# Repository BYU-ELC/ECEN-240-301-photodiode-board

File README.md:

# ECEN-240-301-photodiode-board

Welcome! This repository holds the files for the ECEN 240/301 photodiode board

## Purpose

This repository is meant primarily for internal communication. Under normal circumstances, students of ECEN 240/301 shouldn't need to download and manipulate these files. Although, they are welcome to do so if the need arises.

## Associated Software

This board was designed on Autodesk Eagle

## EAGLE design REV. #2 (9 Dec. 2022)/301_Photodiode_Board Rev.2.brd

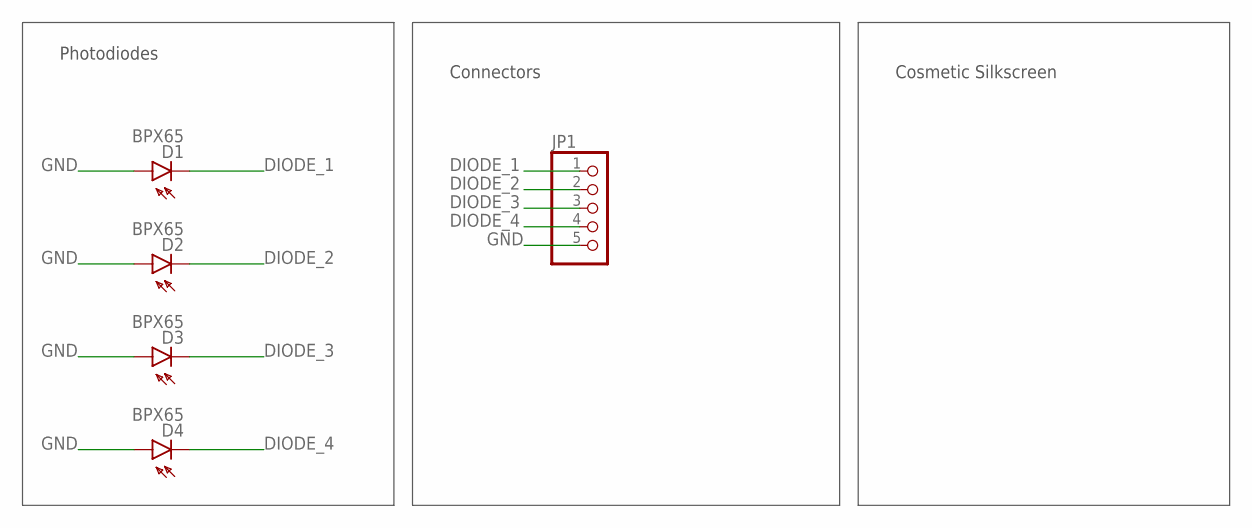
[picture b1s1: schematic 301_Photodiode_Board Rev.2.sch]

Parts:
D1, D2, D3, D4: BPX65
JP1: PINHD-1X5; 1X05

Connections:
DIODE_1: D1.K (C), JP1.1
DIODE_2: D2.K (C), JP1.2
DIODE_3: D3.K (C), JP1.3
DIODE_4: D4.K (C), JP1.4
GND: D1.A, D2.A, D3.A, D4.A, JP1.5

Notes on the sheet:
Photodiodes
Connectors
Cosmetic Silkscreen

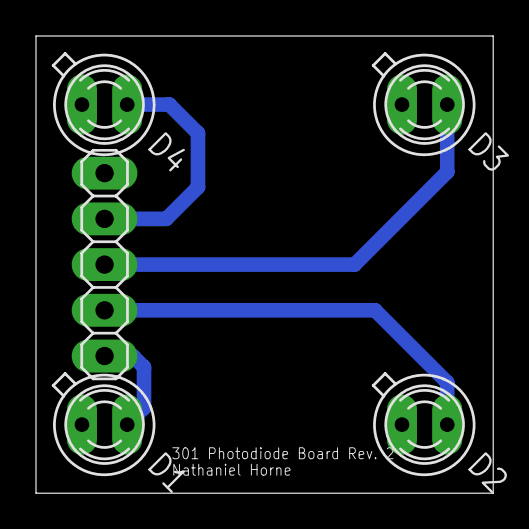
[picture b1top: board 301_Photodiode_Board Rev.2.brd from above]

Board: 2 copper layers, 25.4 x 25.4 mm, 5 parts (0 on the bottom side), 5 nets.

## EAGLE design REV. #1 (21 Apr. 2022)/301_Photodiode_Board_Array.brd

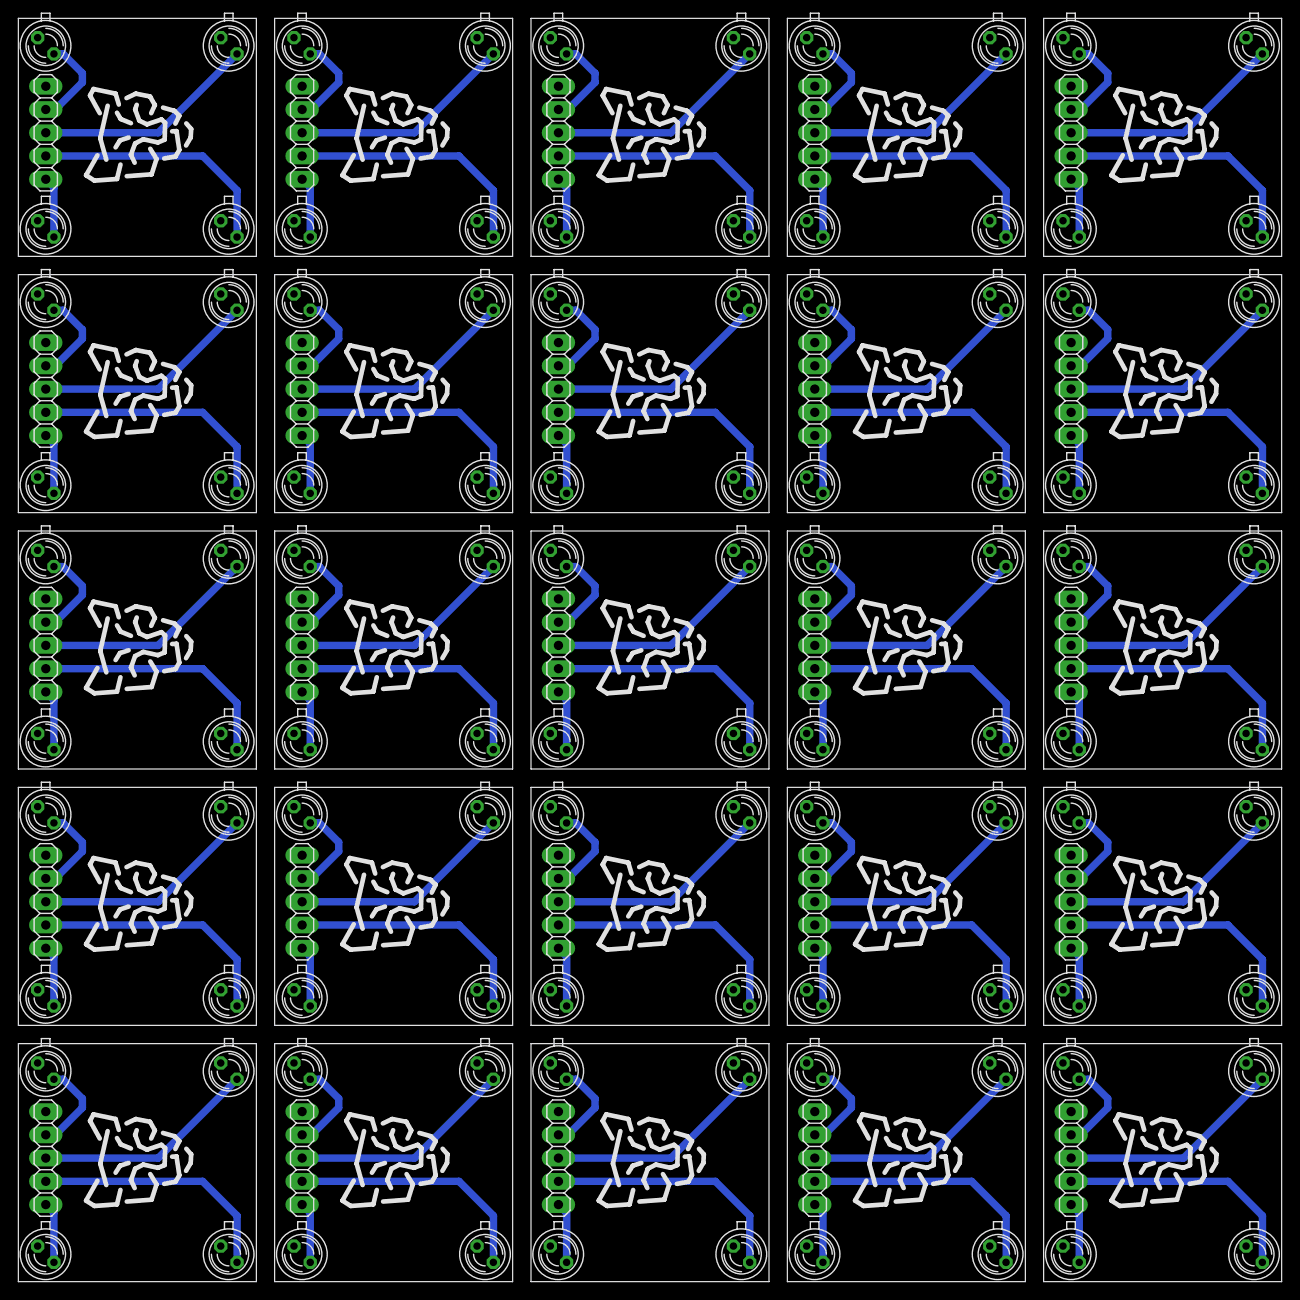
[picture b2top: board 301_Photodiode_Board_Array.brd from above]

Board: 2 copper layers, 138.0 x 138.0 mm, 150 parts (0 on the bottom side), 125 nets.

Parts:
D1, D2, D3, D4, D5, D6, D7, D8, D9, D10, D11, D12, D13, D14, D15, D16, D17, D18, D19, D20, D21, D22, D23, D24, D25, D26, D27, D28, D29, D30, D31, D32, D33, D34, D35, D36, D37, D38, D39, D40, D41, D42, D43, D44, D45, D46, D47, D48, D49, D50, D51, D52, D53, D54, D55, D56, D57, D58, D59, D60, D61, D62, D63, D64, D65, D66, D67, D68, D69, D70, D71, D72, D73, D74, D75, D76, D77, D78, D79, D80, D81, D82, D83, D84, D85, D86, D87, D88, D89, D90, D91, D92, D93, D94, D95, D96, D97, D98, D99, D100: BPX65
JP1, JP2, JP3, JP4, JP5, JP6, JP7, JP8, JP9, JP10, JP11, JP12, JP13, JP14, JP15, JP16, JP17, JP18, JP19, JP20, JP21, JP22, JP23, JP24, JP25: 1X05
U$1, U$2, U$3, U$4, U$5, U$6, U$7, U$8, U$9, U$10, U$11, U$12, U$13, U$14, U$15, U$16, U$17, U$18, U$19, U$20, U$21, U$22, U$23, U$24, U$25: COUGAR_LOGO_LARGE; LRG_COUGAR

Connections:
DIODE_1: D1.K, JP1.1
DIODE_2: D2.K, JP1.2
DIODE_3: D3.K, JP1.3
DIODE_4: D4.K, JP1.4
DIODE_5: D5.K, JP2.1
DIODE_6: D6.K, JP2.2
DIODE_7: D7.K, JP2.3
DIODE_8: D8.K, JP2.4
DIODE_9: D9.K, JP3.1
DIODE_10: D10.K, JP3.2
DIODE_11: D11.K, JP3.3
DIODE_12: D12.K, JP3.4
DIODE_13: D13.K, JP4.1
DIODE_14: D14.K, JP4.2
DIODE_15: D15.K, JP4.3
DIODE_16: D16.K, JP4.4
DIODE_17: D17.K, JP5.1
DIODE_18: D18.K, JP5.2
DIODE_19: D19.K, JP5.3
DIODE_20: D20.K, JP5.4
DIODE_21: D21.K, JP6.1
DIODE_22: D22.K, JP6.2
DIODE_23: D23.K, JP6.3
DIODE_24: D24.K, JP6.4
DIODE_25: D25.K, JP7.1
DIODE_26: D26.K, JP7.2
DIODE_27: D27.K, JP7.3
DIODE_28: D28.K, JP7.4
DIODE_29: D29.K, JP8.1
DIODE_30: D30.K, JP8.2
DIODE_31: D31.K, JP8.3
DIODE_32: D32.K, JP8.4
DIODE_33: D33.K, JP9.1
DIODE_34: D34.K, JP9.2
DIODE_35: D35.K, JP9.3
DIODE_36: D36.K, JP9.4
DIODE_37: D37.K, JP10.1
DIODE_38: D38.K, JP10.2
DIODE_39: D39.K, JP10.3
DIODE_40: D40.K, JP10.4
DIODE_41: D41.K, JP11.1
DIODE_42: D42.K, JP11.2
DIODE_43: D43.K, JP11.3
DIODE_44: D44.K, JP11.4
DIODE_45: D45.K, JP12.1
DIODE_46: D46.K, JP12.2
DIODE_47: D47.K, JP12.3
DIODE_48: D48.K, JP12.4
DIODE_49: D49.K, JP13.1
DIODE_50: D50.K, JP13.2
DIODE_51: D51.K, JP13.3
DIODE_52: D52.K, JP13.4
DIODE_53: D53.K, JP14.1
DIODE_54: D54.K, JP14.2
DIODE_55: D55.K, JP14.3
DIODE_56: D56.K, JP14.4
DIODE_57: D57.K, JP15.1
DIODE_58: D58.K, JP15.2
DIODE_59: D59.K, JP15.3
DIODE_60: D60.K, JP15.4
DIODE_61: D61.K, JP16.1
DIODE_62: D62.K, JP16.2
DIODE_63: D63.K, JP16.3
DIODE_64: D64.K, JP16.4
DIODE_65: D65.K, JP17.1
DIODE_66: D66.K, JP17.2
DIODE_67: D67.K, JP17.3
DIODE_68: D68.K, JP17.4
DIODE_69: D69.K, JP18.1
DIODE_70: D70.K, JP18.2
DIODE_71: D71.K, JP18.3
DIODE_72: D72.K, JP18.4
DIODE_73: D73.K, JP19.1
DIODE_74: D74.K, JP19.2
DIODE_75: D75.K, JP19.3
DIODE_76: D76.K, JP19.4
DIODE_77: D77.K, JP20.1
DIODE_78: D78.K, JP20.2
DIODE_79: D79.K, JP20.3
DIODE_80: D80.K, JP20.4
DIODE_81: D81.K, JP21.1
DIODE_82: D82.K, JP21.2
DIODE_83: D83.K, JP21.3
DIODE_84: D84.K, JP21.4
DIODE_85: D85.K, JP22.1
DIODE_86: D86.K, JP22.2
DIODE_87: D87.K, JP22.3
DIODE_88: D88.K, JP22.4
DIODE_89: D89.K, JP23.1
DIODE_90: D90.K, JP23.2
DIODE_91: D91.K, JP23.3
DIODE_92: D92.K, JP23.4
DIODE_93: D93.K, JP24.1
DIODE_94: D94.K, JP24.2
DIODE_95: D95.K, JP24.3
DIODE_96: D96.K, JP24.4
DIODE_97: D97.K, JP25.1
DIODE_98: D98.K, JP25.2
DIODE_99: D99.K, JP25.3
DIODE_100: D100.K, JP25.4
GND: D1.A, D2.A, D3.A, D4.A, JP1.5
GND1: D5.A, D6.A, D7.A, D8.A, JP2.5
GND2: D9.A, D10.A, D11.A, D12.A, JP3.5
GND3: D13.A, D14.A, D15.A, D16.A, JP4.5
GND4: D17.A, D18.A, D19.A, D20.A, JP5.5
GND5: D21.A, D22.A, D23.A, D24.A, JP6.5
GND6: D25.A, D26.A, D27.A, D28.A, JP7.5
GND7: D29.A, D30.A, D31.A, D32.A, JP8.5
GND8: D33.A, D34.A, D35.A, D36.A, JP9.5
GND9: D37.A, D38.A, D39.A, D40.A, JP10.5
GND10: D41.A, D42.A, D43.A, D44.A, JP11.5
GND11: D45.A, D46.A, D47.A, D48.A, JP12.5
GND12: D49.A, D50.A, D51.A, D52.A, JP13.5
GND13: D53.A, D54.A, D55.A, D56.A, JP14.5
GND14: D57.A, D58.A, D59.A, D60.A, JP15.5
GND15: D61.A, D62.A, D63.A, D64.A, JP16.5
GND16: D65.A, D66.A, D67.A, D68.A, JP17.5
GND17: D69.A, D70.A, D71.A, D72.A, JP18.5
GND18: D73.A, D74.A, D75.A, D76.A, JP19.5
GND19: D77.A, D78.A, D79.A, D80.A, JP20.5
GND20: D81.A, D82.A, D83.A, D84.A, JP21.5
GND21: D85.A, D86.A, D87.A, D88.A, JP22.5
GND22: D89.A, D90.A, D91.A, D92.A, JP23.5
GND23: D93.A, D94.A, D95.A, D96.A, JP24.5
GND24: D97.A, D98.A, D99.A, D100.A, JP25.5

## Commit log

2023-10-04 Enumerate README file
2023-10-04 Add board files from local machine
